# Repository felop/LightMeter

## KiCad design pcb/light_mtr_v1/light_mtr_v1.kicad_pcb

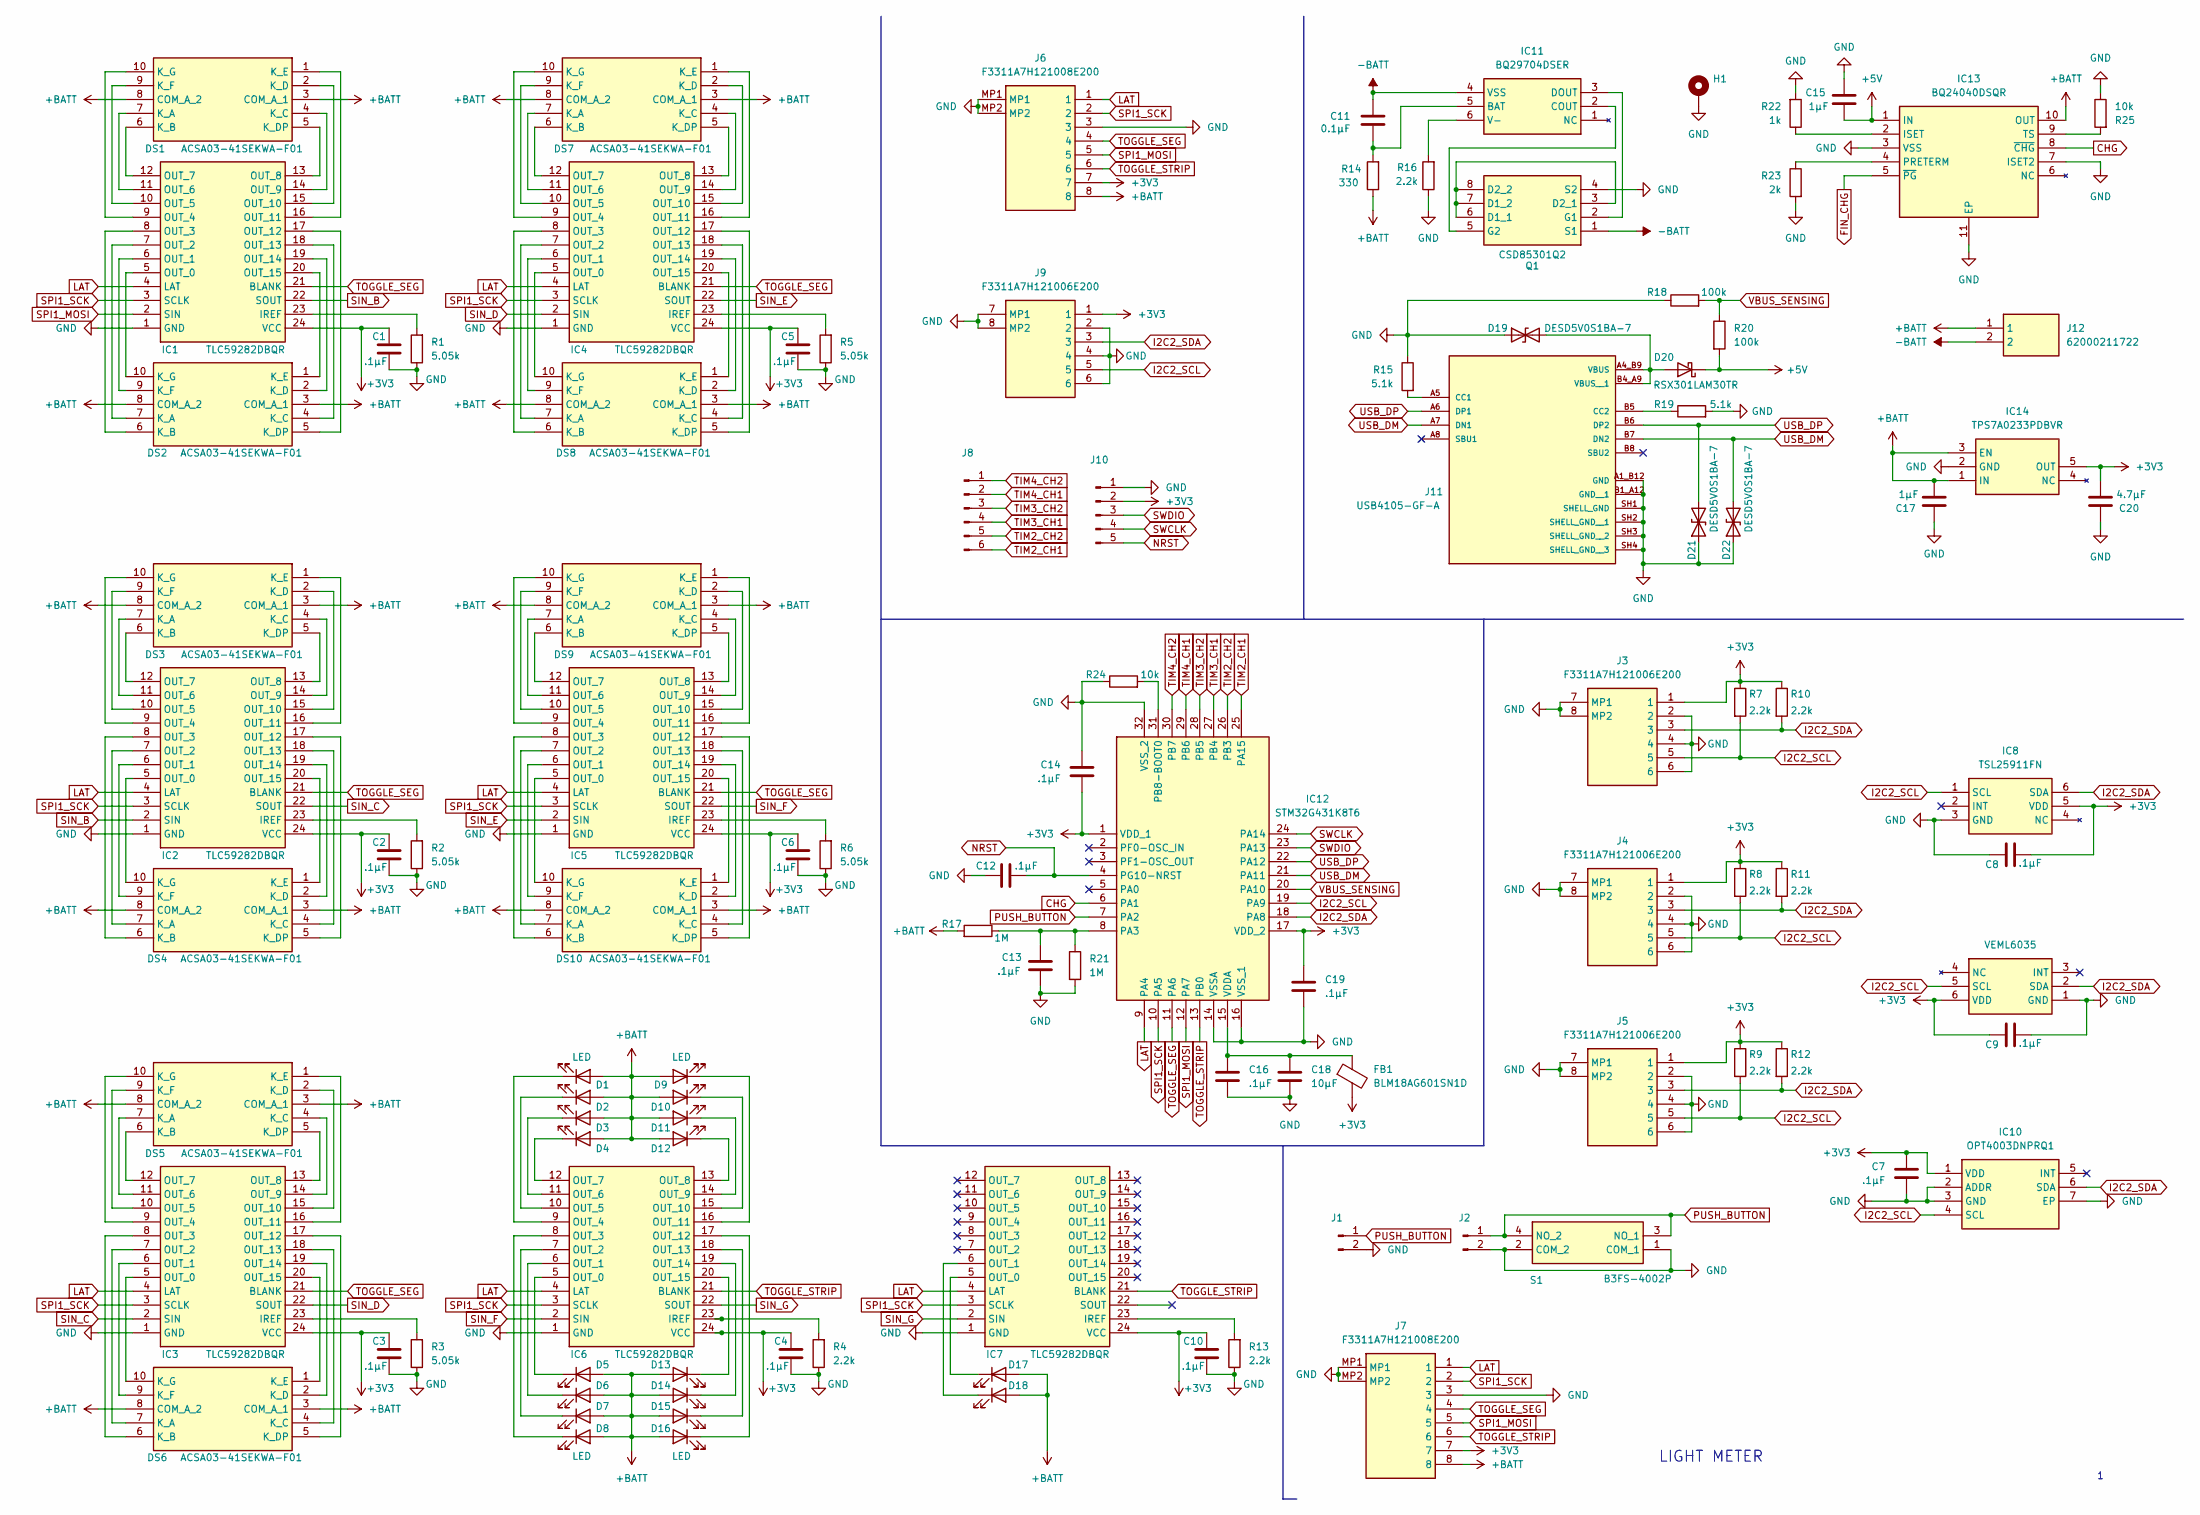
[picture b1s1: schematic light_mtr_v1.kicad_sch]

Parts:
C1, C2, C3, C4, C5, C6, C7, C8, C9, C10, C12, C13, C14, C16, C19: .1µF; C_0603_1608Metric
C11: 0.1µF; C_0603_1608Metric
C15, C17: 1µF; C_0603_1608Metric
C18: 10µF; C_0603_1608Metric
C20: 4.7µF; C_0603_1608Metric
D1, D2, D3, D4, D5, D6, D7, D8, D9, D10, D11, D12, D13, D14, D15, D16, D17, D18: LED; SM1204UAC
D19, D21, D22: DESD5V0S1BA-7; SOD2513X120N
D20: RSX301LAM30TR; DIO_RB050LAM_ROM
DS1, DS2, DS3, DS4, DS5, DS6, DS7, DS8, DS9, DS10: ACSA03-41SEKWA-F01; ACSA0341SEKWAF01; Mouser Part Number 604-ACSA03-41SEKWA
FB1: BLM18AG601SN1D; BLM18SP221SN1B
H1: MountingHole_Pad; MountingHole_2.2mm_M2_DIN965_Pad
IC1, IC2, IC3, IC4, IC5, IC6, IC7: TLC59282DBQR; SOP64P600X175-24N; Mouser Part Number 595-TLC59282DBQR
IC8: TSL25911FN; Mouser Part Number 985-TSL25911FN
IC9: VEML6035; Mouser Part Number 78-VEML6035
IC10: OPT4003DNPRQ1; Mouser Part Number 595-OPT4003DNPRQ1
IC11: BQ29704DSER; SON50P150X150X80-6N; Mouser Part Number 595-BQ29704DSER
IC12: STM32G431K8T6; QFP80P900X900X160-32N; Mouser Part Number 511-STM32G431K8T6
IC13: BQ24040DSQR; SON40P200X200X80-11N; Mouser Part Number 595-BQ24040DSQR
IC14: TPS7A0233PDBVR; SOT95P280X145-5N; Mouser Part Number 595-TPS7A0222PDBVR
J1, J2: Conn_01x02_Pin; PinHeader_1x02_P2.54mm_Vertical
J3, J4, J5, J9: F3311A7H121006E200; Manufacturer_Part_Number F3311A7H121006E200
J6, J7: F3311A7H121008E200; Manufacturer_Part_Number F3311A7H121008E200
J8: Conn_01x06_Pin; PinHeader_1x06_P2.54mm_Vertical
J10: Conn_01x05_Pin; PinHeader_1x05_P2.54mm_Vertical
J11: USB4105-GF-A; PARTREV B4
J12: 62000211722; Mouser Part Number 710-62000211722
Q1: CSD85301Q2; Mouser Part Number 595-CSD85301Q2
R1, R2, R3, R5, R6: 5.05k; R_0603_1608Metric
R4, R13, R16: 2.2k; R_0603_1608Metric
R7, R8, R9, R10, R11, R12: 2.2k; R_0805_2012Metric
R14: 330; R_0603_1608Metric
R15, R19: 5.1k; R_0805_2012Metric
R17, R21: 1M; R_0805_2012Metric
R18, R20: 100k; R_0805_2012Metric
R22: 1k; R_0603_1608Metric
R23: 2k; R_0603_1608Metric
R24, R25: 10k; R_0603_1608Metric
S1: B3FS-4002P; B3FS4002P; Mouser Part Number 653-B3FS-4002P

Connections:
+3V3: C1.1, C2.1, C3.1, C4.1, C5.1, C6.1, C7.1, C8.2, C9.1, C10.1, C14.2, C19.1, C20.2, FB1.2, IC1.24 (VCC), IC2.24 (VCC), IC3.24 (VCC), IC4.24 (VCC), IC5.24 (VCC), IC6.24 (VCC), IC7.24 (VCC), IC8.5 (VDD), IC9.6 (VDD), IC10.1 (VDD), IC12.1 (VDD_1), IC12.17 (VDD_2), IC14.5 (OUT), J3.1, J4.1, J5.1, J6.7, J7.7, J9.1, J10.2, R7.1, R8.1, R9.1, R10.1, R11.1, R12.1
+5V: C15.2, D20.1 (K), IC13.1 (IN), R20.2
+BATT: C17.2, D1.2 (A), D2.2 (A), D3.2 (A), D4.2 (A), D5.2 (A), D6.2 (A), D7.2 (A), D8.2 (A), D9.2 (A), D10.2 (A), D11.2 (A), D12.2 (A), D13.2 (A), D14.2 (A), D15.2 (A), D16.2 (A), D17.2 (A), D18.2 (A), DS1.3 (COM_A_1), DS1.8 (COM_A_2), DS2.3 (COM_A_1), DS2.8 (COM_A_2), DS3.3 (COM_A_1), DS3.8 (COM_A_2), DS4.3 (COM_A_1), DS4.8 (COM_A_2), DS5.3 (COM_A_1), DS5.8 (COM_A_2), DS6.3 (COM_A_1), DS6.8 (COM_A_2), DS7.3 (COM_A_1), DS7.8 (COM_A_2), DS8.3 (COM_A_1), DS8.8 (COM_A_2), DS9.3 (COM_A_1), DS9.8 (COM_A_2), DS10.3 (COM_A_1), DS10.8 (COM_A_2), IC13.10 (OUT), IC14.1 (IN), IC14.3 (EN), J6.8, J7.8, J12.1, R14.1, R17.2
-BATT: C11.2, IC11.4 (VSS), J12.2, Q1.1 (S1)
CHG: IC12.6 (PA1), IC13.8 (~CHG)
FIN_CHG: IC13.5 (~PG)
GND: C1.2, C2.2, C3.2, C4.2, C5.2, C6.2, C7.2, C8.1, C9.2, C10.2, C12.2, C13.2, C14.1, C15.1, C16.2, C17.1, C18.2, C19.2, C20.1, D19.1 (A1), D21.1 (A1), D22.1 (A1), H1.1 (1_1), IC1.1 (GND), IC2.1 (GND), IC3.1 (GND), IC4.1 (GND), IC5.1 (GND), IC6.1 (GND), IC7.1 (GND), IC8.3 (GND), IC9.1 (GND), IC10.2 (ADDR), IC10.3 (GND), IC10.7 (EP), IC12.14 (VSSA), IC12.16 (VSS_1), IC12.32 (VSS_2), IC13.3 (VSS), IC13.7 (ISET2), IC13.11 (EP), IC14.2 (GND), J1.2, J2.2, J3.2, J3.4, J3.6, J3.7 (MP1), J3.8 (MP2), J4.2, J4.4, J4.6, J4.7 (MP1), J4.8 (MP2), J5.2, J5.4, J5.6, J5.7 (MP1), J5.8 (MP2), J6.3, J6.MP1, J6.MP2, J7.3, J7.MP1, J7.MP2, J9.2, J9.4, J9.6, J9.7 (MP1), J9.8 (MP2), J10.1, J11.A1_B12 (GND), J11.B1_A12 (GND__1), J11.SH1 (SHELL_GND), J11.SH2 (SHELL_GND__1), J11.SH3 (SHELL_GND__2), J11.SH4 (SHELL_GND__3), Q1.4 (S2), R1.1, R2.1, R3.1, R4.1, R5.1, R6.1, R13.1, R15.1, R16.1, R18.1, R19.2, R21.2, R22.2, R23.2, R24.1, R25.1, S1.1 (COM_1), S1.2 (COM_2)
I2C2_SCL: IC8.1 (SCL), IC9.5 (SCL), IC10.4 (SCL), IC12.19 (PA9), J3.5, J4.5, J5.5, J9.5, R7.2, R8.2, R9.2
I2C2_SDA: IC8.6 (SDA), IC9.2 (SDA), IC10.6 (SDA), IC12.18 (PA8), J3.3, J4.3, J5.3, J9.3, R10.2, R11.2, R12.2
LAT: IC1.4 (LAT), IC2.4 (LAT), IC3.4 (LAT), IC4.4 (LAT), IC5.4 (LAT), IC6.4 (LAT), IC7.4 (LAT), IC12.9 (PA4), J6.1, J7.1
NRST: C12.1, IC12.4 (PG10-NRST), J10.5
unnamed: D1.1 (K), IC6.9 (OUT_4)
unnamed: D2.1 (K), IC6.10 (OUT_5)
unnamed: D3.1 (K), IC6.11 (OUT_6)
unnamed: D4.1 (K), IC6.12 (OUT_7)
unnamed: D5.1 (K), IC6.5 (OUT_0)
unnamed: D6.1 (K), IC6.6 (OUT_1)
unnamed: D7.1 (K), IC6.7 (OUT_2)
unnamed: D8.1 (K), IC6.8 (OUT_3)
unnamed: D9.1 (K), IC6.16 (OUT_11)
unnamed: D10.1 (K), IC6.15 (OUT_10)
unnamed: D11.1 (K), IC6.14 (OUT_9)
unnamed: D12.1 (K), IC6.13 (OUT_8)
unnamed: D13.1 (K), IC6.20 (OUT_15)
unnamed: D14.1 (K), IC6.19 (OUT_14)
unnamed: D15.1 (K), IC6.18 (OUT_13)
unnamed: D16.1 (K), IC6.17 (OUT_12)
unnamed: D17.1 (K), IC7.5 (OUT_0)
unnamed: D18.1 (K), IC7.6 (OUT_1)
unnamed: D19.2 (A2), D20.2 (A), J11.A4_B9 (VBUS), J11.B4_A9 (VBUS__1)
unnamed: DS1.7 (K_A), IC1.11 (OUT_6)
unnamed: DS1.6 (K_B), IC1.12 (OUT_7)
unnamed: DS1.4 (K_C), IC1.14 (OUT_9)
unnamed: DS1.2 (K_D), IC1.15 (OUT_10)
unnamed: DS1.5 (K_DP), IC1.13 (OUT_8)
unnamed: DS1.1 (K_E), IC1.16 (OUT_11)
unnamed: DS1.9 (K_F), IC1.10 (OUT_5)
unnamed: DS1.10 (K_G), IC1.9 (OUT_4)
unnamed: DS2.7 (K_A), IC1.7 (OUT_2)
unnamed: DS2.6 (K_B), IC1.8 (OUT_3)
unnamed: DS2.4 (K_C), IC1.18 (OUT_13)
unnamed: DS2.2 (K_D), IC1.19 (OUT_14)
unnamed: DS2.5 (K_DP), IC1.17 (OUT_12)
unnamed: DS2.1 (K_E), IC1.20 (OUT_15)
unnamed: DS2.9 (K_F), IC1.6 (OUT_1)
unnamed: DS2.10 (K_G), IC1.5 (OUT_0)
unnamed: DS3.7 (K_A), IC2.11 (OUT_6)
unnamed: DS3.6 (K_B), IC2.12 (OUT_7)
unnamed: DS3.4 (K_C), IC2.14 (OUT_9)
unnamed: DS3.2 (K_D), IC2.15 (OUT_10)
unnamed: DS3.5 (K_DP), IC2.13 (OUT_8)
unnamed: DS3.1 (K_E), IC2.16 (OUT_11)
unnamed: DS3.9 (K_F), IC2.10 (OUT_5)
unnamed: DS3.10 (K_G), IC2.9 (OUT_4)
unnamed: DS4.7 (K_A), IC2.7 (OUT_2)
unnamed: DS4.6 (K_B), IC2.8 (OUT_3)
unnamed: DS4.4 (K_C), IC2.18 (OUT_13)
unnamed: DS4.2 (K_D), IC2.19 (OUT_14)
unnamed: DS4.5 (K_DP), IC2.17 (OUT_12)
unnamed: DS4.1 (K_E), IC2.20 (OUT_15)
unnamed: DS4.9 (K_F), IC2.6 (OUT_1)
unnamed: DS4.10 (K_G), IC2.5 (OUT_0)
unnamed: DS5.7 (K_A), IC3.11 (OUT_6)
unnamed: DS5.6 (K_B), IC3.12 (OUT_7)
unnamed: DS5.4 (K_C), IC3.14 (OUT_9)
unnamed: DS5.2 (K_D), IC3.15 (OUT_10)
unnamed: DS5.5 (K_DP), IC3.13 (OUT_8)
unnamed: DS5.1 (K_E), IC3.16 (OUT_11)
unnamed: DS5.9 (K_F), IC3.10 (OUT_5)
unnamed: DS5.10 (K_G), IC3.9 (OUT_4)
unnamed: DS6.7 (K_A), IC3.7 (OUT_2)
unnamed: DS6.6 (K_B), IC3.8 (OUT_3)
unnamed: DS6.4 (K_C), IC3.18 (OUT_13)
unnamed: DS6.2 (K_D), IC3.19 (OUT_14)
unnamed: DS6.5 (K_DP), IC3.17 (OUT_12)
unnamed: DS6.1 (K_E), IC3.20 (OUT_15)
unnamed: DS6.9 (K_F), IC3.6 (OUT_1)
unnamed: DS6.10 (K_G), IC3.5 (OUT_0)
unnamed: DS7.7 (K_A), IC4.11 (OUT_6)
unnamed: DS7.6 (K_B), IC4.12 (OUT_7)
unnamed: DS7.4 (K_C), IC4.14 (OUT_9)
unnamed: DS7.2 (K_D), IC4.15 (OUT_10)
unnamed: DS7.5 (K_DP), IC4.13 (OUT_8)
unnamed: DS7.1 (K_E), IC4.16 (OUT_11)
unnamed: DS7.9 (K_F), IC4.10 (OUT_5)
unnamed: DS7.10 (K_G), IC4.9 (OUT_4)
unnamed: DS8.7 (K_A), IC4.7 (OUT_2)
unnamed: DS8.6 (K_B), IC4.8 (OUT_3)
unnamed: DS8.4 (K_C), IC4.18 (OUT_13)
unnamed: DS8.2 (K_D), IC4.19 (OUT_14)
unnamed: DS8.5 (K_DP), IC4.17 (OUT_12)
unnamed: DS8.1 (K_E), IC4.20 (OUT_15)
unnamed: DS8.9 (K_F), IC4.6 (OUT_1)
unnamed: DS8.10 (K_G), IC4.5 (OUT_0)
unnamed: DS9.7 (K_A), IC5.11 (OUT_6)
unnamed: DS9.6 (K_B), IC5.12 (OUT_7)
unnamed: DS9.4 (K_C), IC5.14 (OUT_9)
unnamed: DS9.2 (K_D), IC5.15 (OUT_10)
unnamed: DS9.5 (K_DP), IC5.13 (OUT_8)
unnamed: DS9.1 (K_E), IC5.16 (OUT_11)
unnamed: DS9.9 (K_F), IC5.10 (OUT_5)
unnamed: DS9.10 (K_G), IC5.9 (OUT_4)
unnamed: DS10.7 (K_A), IC5.7 (OUT_2)
unnamed: DS10.6 (K_B), IC5.8 (OUT_3)
unnamed: DS10.4 (K_C), IC5.18 (OUT_13)
unnamed: DS10.2 (K_D), IC5.19 (OUT_14)
unnamed: DS10.5 (K_DP), IC5.17 (OUT_12)
unnamed: DS10.1 (K_E), IC5.20 (OUT_15)
unnamed: DS10.9 (K_F), IC5.6 (OUT_1)
unnamed: DS10.10 (K_G), IC5.5 (OUT_0)
unnamed: IC1.23 (IREF), R1.2
unnamed: IC2.23 (IREF), R2.2
unnamed: IC3.23 (IREF), R3.2
unnamed: IC4.23 (IREF), R5.2
unnamed: IC5.23 (IREF), R6.2
unnamed: IC6.23 (IREF), R4.2
unnamed: IC7.23 (IREF), R13.2
unnamed: C11.1, IC11.5 (BAT), R14.2
unnamed: IC11.2 (COUT), Q1.5 (G2)
unnamed: IC11.3 (DOUT), Q1.2 (G1)
unnamed: IC11.6 (V-), R16.2
unnamed: C13.1, IC12.8 (PA3), R17.1, R21.1
unnamed: IC12.31 (PB8-BOOT0), R24.2
unnamed: C16.1, C18.1, FB1.1, IC12.15 (VDDA)
unnamed: IC13.2 (ISET), R22.1
unnamed: IC13.4 (PRETERM), R23.1
unnamed: IC13.9 (TS), R25.2
unnamed: J11.A5 (CC1), R15.2
unnamed: J11.B5 (CC2), R19.1
unnamed: Q1.3 (D2_1), Q1.6 (D1_1), Q1.7 (D1_2), Q1.8 (D2_2)
PUSH_BUTTON: IC12.7 (PA2), J1.1, J2.1, S1.3 (NO_1), S1.4 (NO_2)
SIN_B: IC1.22 (SOUT), IC2.2 (SIN)
SIN_C: IC2.22 (SOUT), IC3.2 (SIN)
SIN_D: IC3.22 (SOUT), IC4.2 (SIN)
SIN_E: IC4.22 (SOUT), IC5.2 (SIN)
SIN_F: IC5.22 (SOUT), IC6.2 (SIN)
SIN_G: IC6.22 (SOUT), IC7.2 (SIN)
SPI1_MOSI: IC1.2 (SIN), IC12.12 (PA7), J6.5, J7.5
SPI1_SCK: IC1.3 (SCLK), IC2.3 (SCLK), IC3.3 (SCLK), IC4.3 (SCLK), IC5.3 (SCLK), IC6.3 (SCLK), IC7.3 (SCLK), IC12.10 (PA5), J6.2, J7.2
SWCLK: IC12.24 (PA14), J10.4
SWDIO: IC12.23 (PA13), J10.3
TIM2_CH1: IC12.25 (PA15), J8.6
TIM2_CH2: IC12.26 (PB3), J8.5
TIM3_CH1: IC12.27 (PB4), J8.4
TIM3_CH2: IC12.28 (PB5), J8.3
TIM4_CH1: IC12.29 (PB6), J8.2
TIM4_CH2: IC12.30 (PB7), J8.1
TOGGLE_SEG: IC1.21 (BLANK), IC2.21 (BLANK), IC3.21 (BLANK), IC4.21 (BLANK), IC5.21 (BLANK), IC12.11 (PA6), J6.4, J7.4
TOGGLE_STRIP: IC6.21 (BLANK), IC7.21 (BLANK), IC12.13 (PB0), J6.6, J7.6
USB_DM: D22.2 (A2), IC12.21 (PA11), J11.A7 (DN1), J11.B7 (DN2)
USB_DP: D21.2 (A2), IC12.22 (PA12), J11.A6 (DP1), J11.B6 (DP2)
VBUS_SENSING: IC12.20 (PA10), R18.2, R20.1

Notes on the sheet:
LIGHT METER

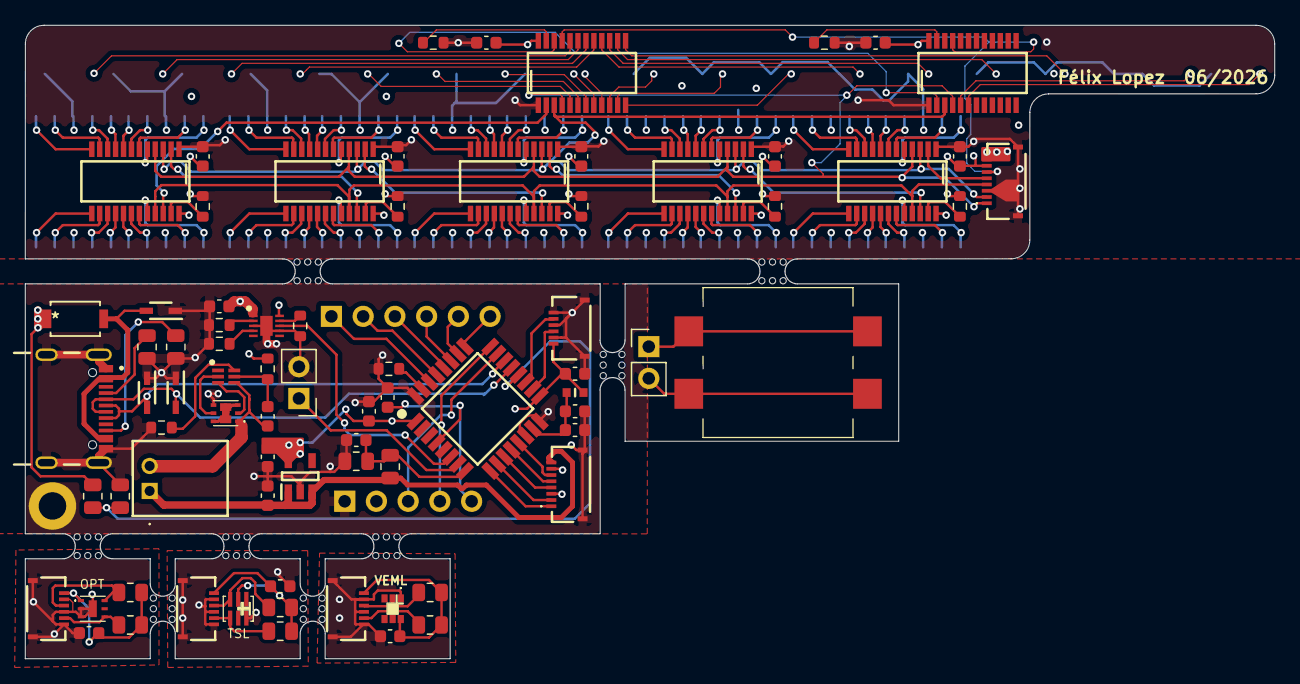
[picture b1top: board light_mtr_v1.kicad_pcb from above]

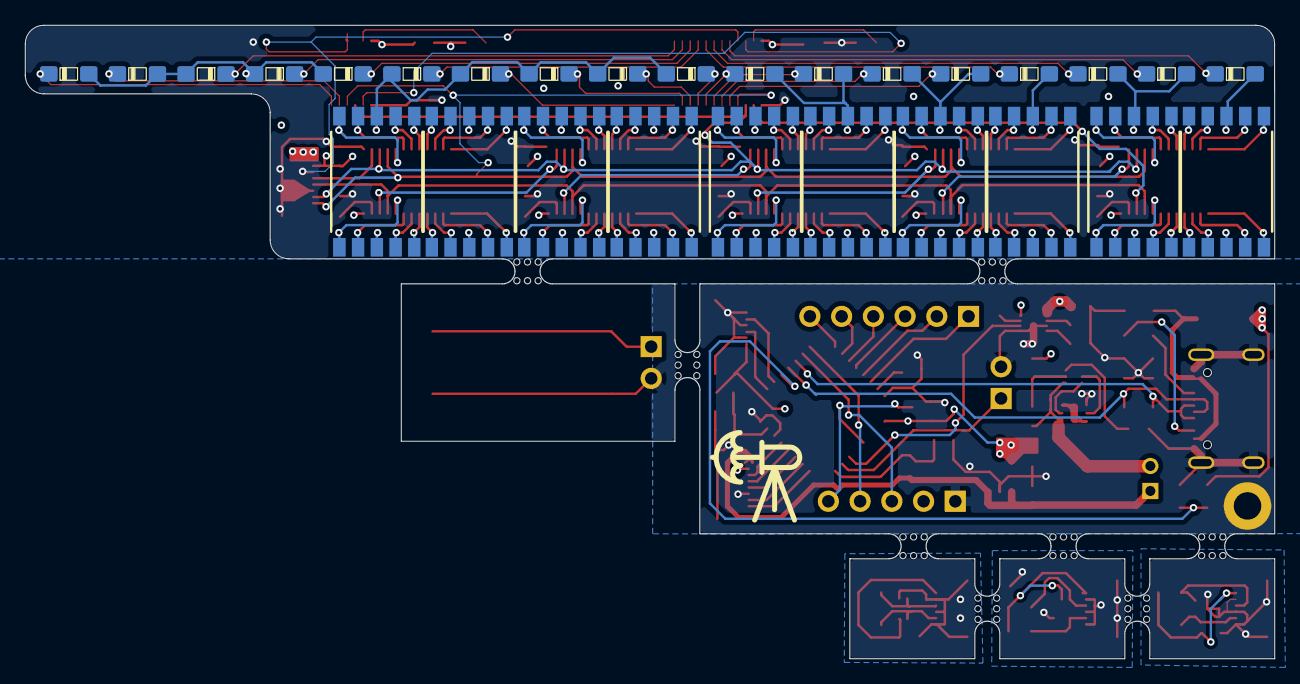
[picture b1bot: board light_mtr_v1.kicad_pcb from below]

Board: 4 copper layers, 100.0 x 50.7 mm, 107 parts (28 on the bottom side), 151 nets.

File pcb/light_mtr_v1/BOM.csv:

"Reference","Qty","Value","DNP","Exclude from BOM","Exclude from Board","Footprint","Datasheet"
"C1,C2,C3,C4,C5,C6,C7,C8,C9,C10,C12,C13,C14,C16,C19","15",".1µF","","","","Capacitor_SMD:C_0603_1608Metric",""
"C11","1","0.1µF","","","","Capacitor_SMD:C_0603_1608Metric",""
"C15,C17","2","1µF","","","","Capacitor_SMD:C_0603_1608Metric",""
"C18","1","10µF","","","","Capacitor_SMD:C_0603_1608Metric",""
"C20","1","4.7µF","","","","Capacitor_SMD:C_0603_1608Metric",""
"D1,D2,D3,D4,D5,D6,D7,D8,D9,D10,D11,D12,D13,D14,D15,D16,D17,D18","18","LED","","","","LIB_SM1204UAC:SM1204UAC",""
"D19,D21,D22","3","DESD5V0S1BA-7","","","","DESD5V0S1BA-7:SOD2513X120N",""
"D20","1","RSX301LAM30TR","","","","RSX301LAM30TR:DIO_RB050LAM_ROM",""
"DS1,DS2,DS3,DS4,DS5,DS6,DS7,DS8,DS9,DS10","10","ACSA03-41SEKWA-F01","","","","ACSA03-41SEKWA-F01:ACSA0341SEKWAF01","https://www.kingbrightusa.com/images/catalog/SPEC/ACSA03-41S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"
"FB1","1","BLM18AG601SN1D","","","","BLM18AG601SN1D:BLM18SP221SN1B",""
"IC1,IC2,IC3,IC4,IC5,IC6,IC7","7","TLC59282DBQR","","","","TLC59282DBQR:SOP64P600X175-24N","http://www.ti.com/lit/gpn/tlc59282"
"IC8","1","TSL25911FN","","","","TSL25911FN:TSL25911FN","http://ams.com/documents/20143/36005/TSL2591_DS000338_6-00.pdf"
"IC9","1","VEML6035","","","","VEML6035:VEML6035","https://www.vishay.com/docs/84889/veml6035.pdf"
"IC10","1","OPT4003DNPRQ1","","","","OPT4003DNPRQ1 2:OPT4003DNPRQ1","https://www.ti.com/lit/ds/symlink/opt4003-q1.pdf?ts=17054999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"
"IC11","1","BQ29704DSER","","","","BQ29704DSER:SON50P150X150X80-6N","https://www.ti.com/lit/ds/symlink/bq2970.pdf?ts=1630903957541"
"IC12","1","STM32G431K8T6","","","","STM32G431K8T6:QFP80P900X900X160-32N","https://www.st.com/resource/en/datasheet/stm32g431c6.pdf"
"IC13","1","BQ24040DSQR","","","","BQ24040DSQR:SON40P200X200X80-11N","http://www.ti.com/lit/gpn/bq24040"
"IC14","1","TPS7A0233PDBVR","","","","TPS7A0222PDBVR:SOT95P280X145-5N",""
"J1,J2","2","Conn_01x02_Pin","","","","Connector_PinHeader_2.54mm:PinHeader_1x02_P2.54mm_Vertical",""
"J3,J4,J5,J9","4","F3311A7H121006E200","","","","F3311A7H121006E200:F3311A7H121006E200","boss20329"
"J6,J7","2","F3311A7H121008E200","","","","F3311A7H121008E200","https://cdn.amphenol-cs.com/media/wysiwyg/files/documentatio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"
"J8","1","Conn_01x06_Pin","","","","Connector_PinHeader_2.54mm:PinHeader_1x06_P2.54mm_Vertical",""
"J10","1","Conn_01x05_Pin","","","","Connector_PinHeader_2.54mm:PinHeader_1x05_P2.54mm_Vertical",""
"J11","1","USB4105-GF-A","","","","USB4105-GF-A:USB4105-GF-A",""
"J12","1","62000211722","","","","62000211722","https://www.we-online.com/catalog/datasheet/62000211722.pdf"
"Q1","1","CSD85301Q2","","","","CSD85301Q2:CSD85301Q2","http://www.ti.com/lit/gpn/csd85301q2"
"R1,R2,R3,R5,R6","5","5.05k","","","","Resistor_SMD:R_0603_1608Metric",""
"R4,R13,R16","3","2.2k","","","","Resistor_SMD:R_0603_1608Metric",""
"R7,R8,R9,R10,R11,R12","6","2.2k","","","","Resistor_SMD:R_0805_2012Metric",""
"R14","1","330","","","","Resistor_SMD:R_0603_1608Metric",""
"R15,R19","2","5.1k","","","","Resistor_SMD:R_0805_2012Metric",""
"R17,R21","2","1M","","","","Resistor_SMD:R_0805_2012Metric",""
"R18,R20","2","100k","","","","Resistor_SMD:R_0805_2012Metric",""
"R22","1","1k","","","","Resistor_SMD:R_0603_1608Metric",""
"R23","1","2k","","","","Resistor_SMD:R_0603_1608Metric",""
"R24,R25","2","10k","","","","Resistor_SMD:R_0603_1608Metric",""
"S1","1","B3FS-4002P","","","","B3FS-4002P:B3FS4002P","https://www.digikey.com/en/products/detail/omron-electronics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"

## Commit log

2026-06-22 added pcb files
